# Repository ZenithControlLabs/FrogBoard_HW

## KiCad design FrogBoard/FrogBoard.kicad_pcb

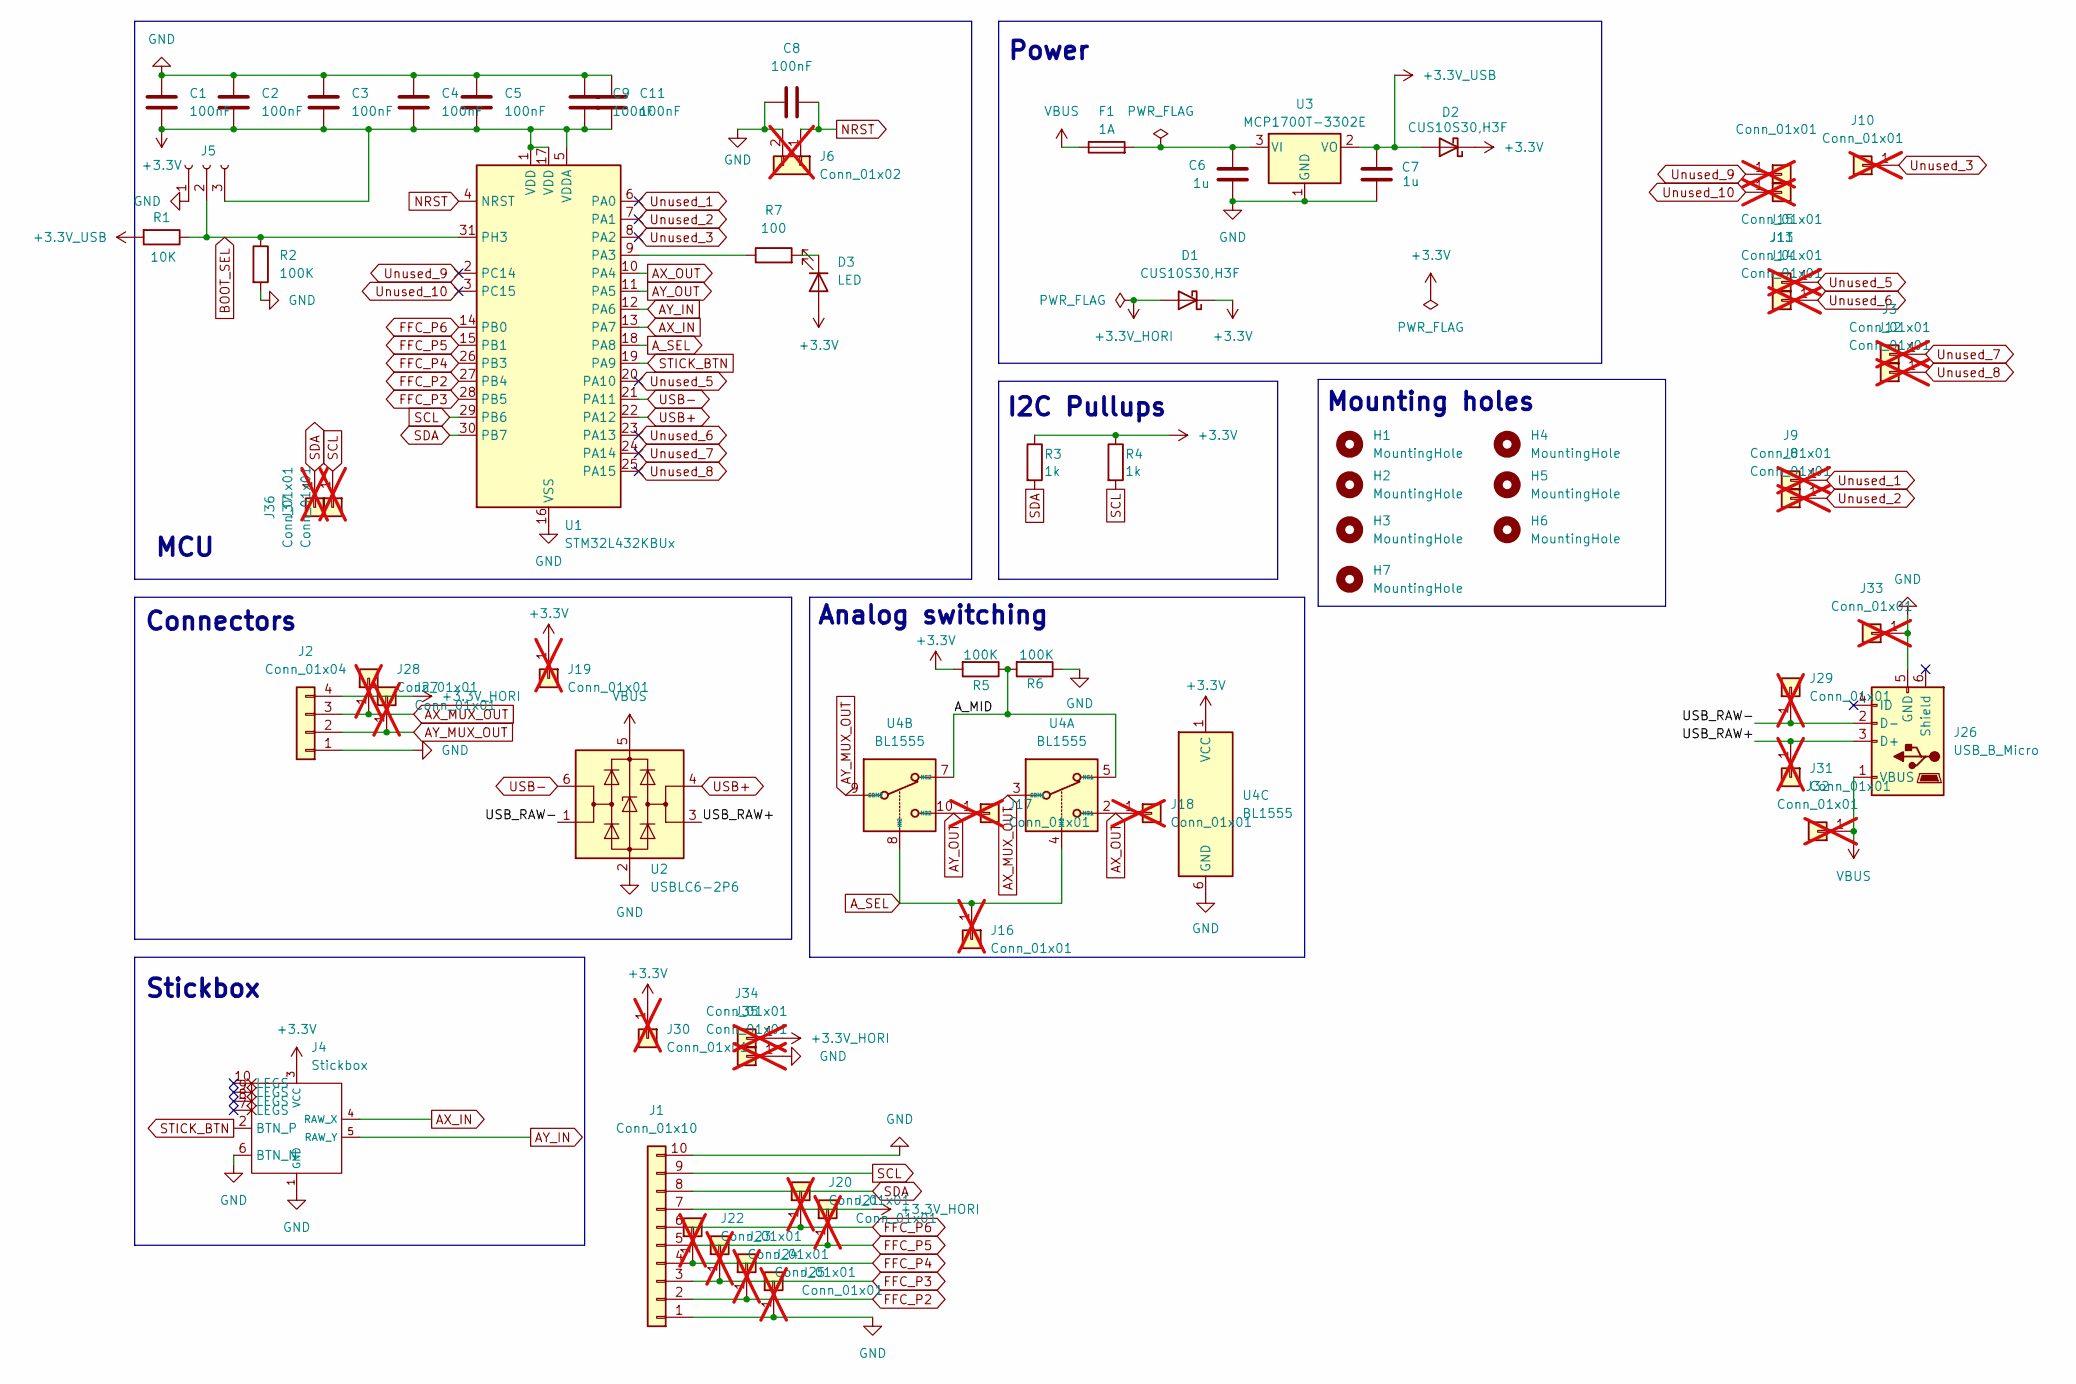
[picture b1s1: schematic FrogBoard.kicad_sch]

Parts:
C1, C2, C3, C4, C5, C8, C9, C11: 100nF; C_0603_1608Metric_Pad1.08x0.95mm_HandSolder; MPN CL10B104KB8NNNC; LCSC C1591
C6, C7: 1u; C_0805_2012Metric_Pad1.18x1.45mm_HandSolder; MPN CL21B105KBFNNNE; LCSC C28323
D1, D2: CUS10S30,H3F; D_SOD-323; MPN CUS10S30,H3F; LCSC C146335
D3: LED; LED_0603_1608Metric; MPN YLED0603R; LCSC C19171390
F1: 1A; Fuse_1206_3216Metric_Pad1.42x1.75mm_HandSolder; MPN nSMD050-33V; LCSC C70077
H1, H4: MountingHole; MountingHole_2.2mm_M2
H2, H5: MountingHole; MountingHole_1.7mm
H3, H6: MountingHole; MountingHole_2.833mm
H7: MountingHole; MountingHole_4.5mm
J1: Conn_01x10; CON_5034801000_MOL; MPN 5034801000; LCSC C127355
J2: Conn_01x04; CONN_528070410_MOL; MPN 528070410; LCSC C3170036
J3, J8, J9, J10, J11, J12, J13, J14, J15, J16, J17, J18, J19, J20, J21, J22, J23, J24, J25, J27, J28, J29, J30, J31, J32, J33, J34, J35, J36, J37: Conn_01x01; FrogBoard_PinHeader_1x01_P1.00mm_Vertical; not fitted
J4: Stickbox
J5: Conn_01x03_Socket; PinHeader_1x03_P1.00mm_Vertical
J6: Conn_01x02; PinHeader_1x02_P1.00mm_Vertical_Neutral_No_Coutryard; not fitted
J26: USB_B_Micro; AMPHENOL_10118194-0001LF; MPN 10118194-0001LF; LCSC C132563
R1: 10K; R_0603_1608Metric_Pad0.98x0.95mm_HandSolder; MPN RC0603FR-0710KL; LCSC C98220
R2, R5, R6: 100K; R_0603_1608Metric_Pad0.98x0.95mm_HandSolder; MPN RC0603FR-07100KL; LCSC C14675
R3, R4: 1k; R_0603_1608Metric_Pad0.98x0.95mm_HandSolder; MPN RC0603FR-071KL; LCSC C22548
R7: 100; R_0603_1608Metric; MPN RC0603FR-07100RL; LCSC C105588
U1: STM32L432KBUx; QFN-32-1EP_5x5mm_P0.5mm_EP3.45x3.45mm; MPN STM32L432KBU6TR; LCSC C2928224
U2: USBLC6-2P6; SOT-666; MPN USBLC6-2P6; LCSC C2827693
U3: MCP1700T-3302E; SOT-23; MPN MCP1700T-3302E/TT; LCSC C39051
U4: BL1555; MSOP-10_3x3mm_P0.5mm; MPN BL1555MM; LCSC C2826598

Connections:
+3.3V: C1.2, C2.2, C3.2, C4.2, C5.2, C9.2, C11.2, D1.1 (K), D2.1 (K), D3.2 (A), J4.3 (VCC), J5.3, J19.1, J30.1, R3.1, R4.1, R5.2, U1.1 (VDD), U1.5 (VDDA), U1.17 (VDD), U4.1 (VCC)
+3.3V_HORI: D1.2 (A), J1.7, J2.4, J34.1
+3.3V_USB: C7.2, D2.2 (A), R1.2, U3.2 (VO)
/A_MID: R5.1, R6.2, U4.5 (NC1), U4.7 (NC2)
/USB_RAW+: J26.3 (D+), J31.1, U2.3 (I/O2)
/USB_RAW-: J26.2 (D-), J29.1, U2.1 (I/O1)
AX_IN: J4.4 (RAW_X), U1.13 (PA7)
AX_MUX_OUT: J2.3, J28.1, U4.3 (COM1)
AX_OUT: J18.1, U1.10 (PA4), U4.2 (NO1)
AY_IN: J4.5 (RAW_Y), U1.12 (PA6)
AY_MUX_OUT: J2.2, J27.1, U4.9 (COM2)
AY_OUT: J17.1, U1.11 (PA5), U4.10 (NO2)
A_SEL: J16.1, U1.18 (PA8), U4.4 (IN1), U4.8 (IN2)
BOOT_SEL: J5.2, R1.1, R2.1, U1.31 (PH3)
FFC_P2: J1.2, J24.1, U1.27 (PB4)
FFC_P3: J1.3, J23.1, U1.28 (PB5)
FFC_P4: J1.4, J22.1, U1.26 (PB3)
FFC_P5: J1.5, J21.1, U1.15 (PB1)
FFC_P6: J1.6, J20.1, U1.14 (PB0)
GND: C1.1, C2.1, C3.1, C4.1, C5.1, C6.2, C7.1, C8.1, C9.1, C11.1, J1.1, J1.10, J2.1, J4.1 (GND), J4.6 (BTN_N), J5.1, J6.2, J25.1, J26.5 (GND), J33.1, J35.1, R2.2, R6.1, U1.16 (VSS), U1.32 (VSS), U1.33 (VSS), U2.2 (GND), U3.1 (GND), U4.6 (GND); also elsewhere on the board
NRST: C8.2, J6.1, U1.4 (NRST)
unnamed: D3.1 (K), R7.2
unnamed: R7.1, U1.9 (PA3)
unnamed: C6.1, F1.2, U3.3 (VI)
SCL: J1.9, J37.1, R4.2, U1.29 (PB6)
SDA: J1.8, J36.1, R3.2, U1.30 (PB7)
STICK_BTN: J4.2 (BTN_P), U1.19 (PA9)
USB+: U1.22 (PA12), U2.4 (I/O2)
USB-: U1.21 (PA11), U2.6 (I/O1)
Unused_1: J9.1, U1.6 (PA0)
Unused_2: J8.1, U1.7 (PA1)
Unused_3: J10.1, U1.8 (PA2)
Unused_5: J13.1, U1.20 (PA10)
Unused_6: J14.1, U1.23 (PA13)
Unused_7: J3.1, U1.24 (PA14)
Unused_8: J12.1, U1.25 (PA15)
Unused_9: J15.1, U1.2 (PC14)
Unused_10: J11.1, U1.3 (PC15)
VBUS: F1.1, J26.1 (VBUS), J32.1, U2.5 (VBUS)

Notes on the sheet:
Mounting holes
Power
Connectors
Stickbox
MCU
I2C Pullups
Analog switching

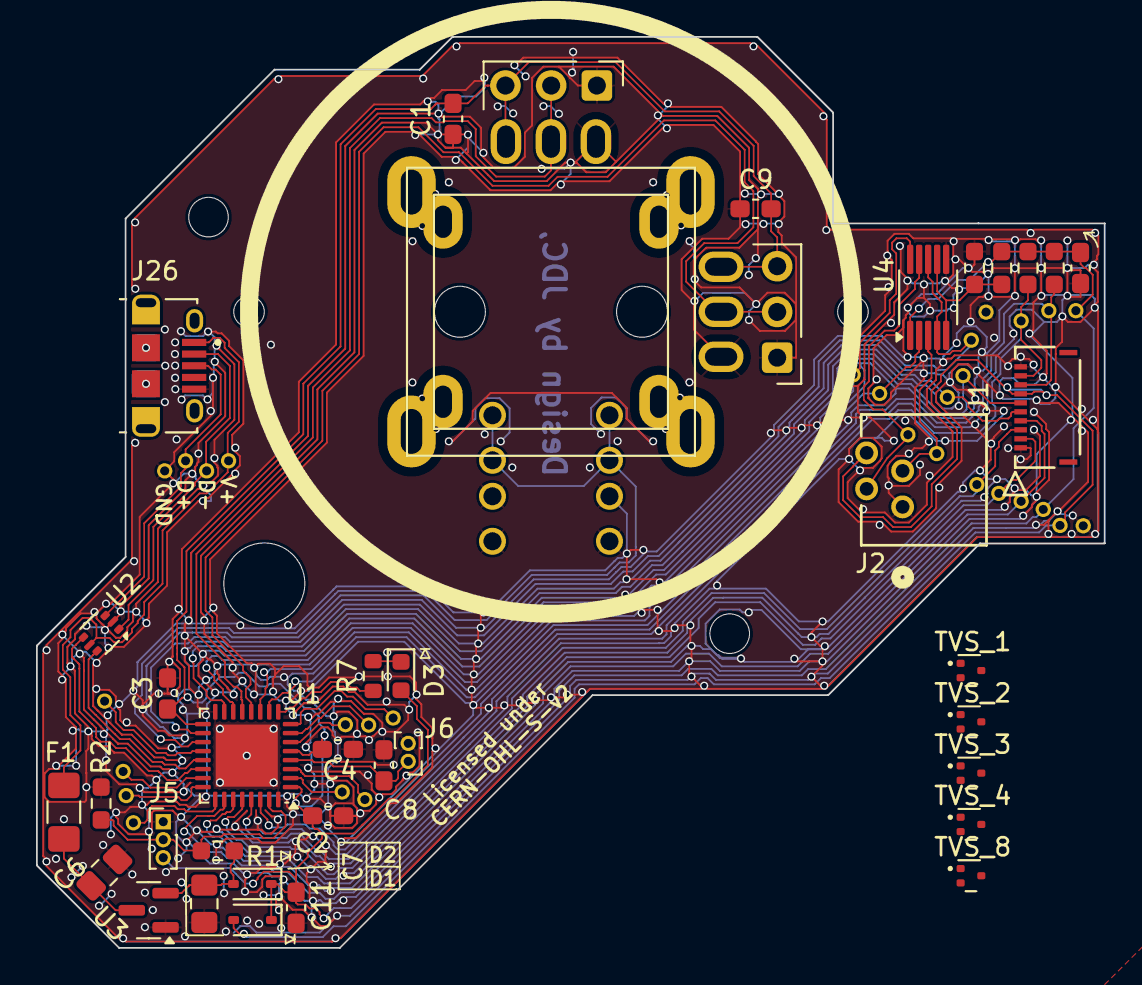
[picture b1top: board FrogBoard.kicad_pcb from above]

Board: 2 copper layers, 59.3 x 50.6 mm, 73 parts (0 on the bottom side), 39 nets.

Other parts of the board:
TVS_1, TVS_2, TVS_3, TVS_4, TVS_8: SZUESD3.3DT5G; SOT-723

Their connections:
GND: TVS_1.3 (common), TVS_2.3 (common), TVS_3.3 (common), TVS_4.3 (common), TVS_8.3 (common); also elsewhere on the board

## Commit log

2025-09-12 [skip ci] initial commit (empty design)
2025-09-12 1st draft of schematic
2025-09-14 PCB outline/initial layout
2025-09-15 Add mux for analog out lines, cleanup schematic
2025-09-15 round out pcb corners
2025-09-21 Cleaned up power filtering, fixed broken symbol and foorpting for mux, and started layout work
2025-09-21 routed the power section, places most ofthe components. Test points still to be added
2025-09-22 Switch to BL1555 analog chip
2025-10-07 first pass at layout
2025-10-07 Add NRST header, clean up silkscreens
2025-10-09 Integrated reset header
2025-10-10 Final board layout cleanup, added I2C testpoints
2025-10-10 Add part numbers, run DRC, add guide
2025-10-10 Fix ERC/DRC
2025-10-10 ignore lib footprint mismatch for kibot ci
2025-10-12 Add notch in board outline for johnny's case; 3d model test
2025-10-13 more ground cleanups and stitching
2025-10-13 more refinement, also added DRC exclussions
2025-10-24 removed filter-cap positions and added testpoints for unused MCU pins
2025-10-26 Add LED
2025-10-29 adding indicator LED
2025-11-11 Replace micro B with USB-C connector
2025-11-18 Cleaned up board edge positions and layed out the main bus
2025-11-26 Update footprint and put back micro USB
2025-11-26 move usb into correct position
2025-12-05 bulk rounting done
2025-12-08 moved MCU south a bit for better routing
2025-12-28 electrically correct
2025-12-28 Should be copper complete
2025-12-30 Fix silkscreens
2026-01-14 Add FrogBoard logo
2026-01-18 Silkscreens and logo
2026-01-19 Grew and adjusted the feet of the stickbox
2026-01-22 drc/erc fixes; fix BOM entries
2026-01-22 drc warning fix
2026-01-24 Change current limiting resistor R7 value to 100 from 1K
2026-01-24 R7 drc fix
2026-01-24 final copper cleanup
2026-01-28 Add silkscreens for J5 and update testing guide
2026-02-01 Adjusted DRC to line up with JLC, adjusted size of VIAs to match JLCs cheapest level, and fixed the DRC issues
2026-03-03 pulled in from board-edge
2026-03-12 goofiest DRC fix ever
2026-03-28 Add 5 TVS diodes

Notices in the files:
FrogBoard/FrogBoard.kicad_pcb:
Licensed under
CERN-OHL-S-v2
